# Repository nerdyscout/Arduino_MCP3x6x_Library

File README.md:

# Arduino MCP3x6x Library

Arduino library for Microchip MCP346xR / MCP356xR 16/24-bit SAR analog-to-digital converters over SPI.

Supports Microchip MCP3461R/MCP3462R/MCP3464R (16-bit) and MCP3561R/MCP3562R/MCP3564R (24-bit) ADC families.

## Features

- Template-based device support — one code base for all six MCP3x6xR variants
- SPI register interface with fast commands (CONVERSION, STANDBY, SHUTDOWN, FULL_SHUTDOWN, RESET, SREAD, IREAD, IWRITE)
- Single-ended and differential channel selection (CH0–CH7, internal channels: OFFSET, VCM, AVDD, TEMP, DIFFx)
- Config0–Config3 register access (gain, OSR, data rate, conversion mode, etc.)
- Continuous conversion and scan modes
- Data-ready (DR) status and data-available polling
- IRQ and MCLK pin attachment
- Offset / gain calibration and temperature conversion helpers
- Low-power modes: standby, shutdown, full shutdown
- PlatformIO-mocked unit tests (ArduinoFake + Unity), hardware smoke tests, and hardware-in-the-loop SPI verification

## Supported devices

| Device | Resolution |
|--------|------------|
| MCP3461R / MCP3462R / MCP3464R | 16-bit |
| MCP3561R / MCP3562R / MCP3564R | 24-bit |

## Quick start

### Installation

**Arduino Library Manager:** search for **MCP3x6xR**.

**Manual / git:**

```sh
git clone https://github.com/nerdyscout/Arduino_MCP3x6x_Library.git \
  ~/Arduino/libraries/MCP3x6xR
```

**PlatformIO:** add to `platformio.ini`:

```ini
lib_deps = nerdyscout/MCP3x6xR
```

### Basic usage

```cpp
#include "Arduino_MCP3x6x_Library.hpp"

MCP3461 mcp;  // or MCP3564, MCP3464, etc.

void setup() {
  mcp.begin();
}

void loop() {
  int32_t raw = mcp.analogRead(MCP3x6x_CH0);
  double volt = raw * mcp.getReference() / mcp.getMaxValue();
  delay(100);
}
```

See `src/Arduino_MCP3x6x_Library.hpp` for the full class API, or build the Doxygen reference (`doxygen Doxyfile`).

## Building and testing

This project uses PlatformIO.

### Build examples

Build all examples for all environments:

```sh
./examples/build.sh
```

Build specific environments:

```sh
./examples/build.sh ESP32 ATMEGA328P SAMD21G18A
```

Build only one example:

```sh
./examples/build.sh MCP3564_DMA
```

Upload a single example to your board:

```sh
./examples/upload.sh MCP3564_DMA ATMEGA328P
```

See `examples/README.md` for full `build.sh` / `upload.sh` usage details.

### Run mocked unit tests (no hardware required)

```sh
pio test -e mocked
```

The mocked environment compiles and executes the same mock test suite for all six MCP variants via `FOR_EACH_ADC` macro expansion, verifying chip-ID validation and per-variant register behavior.

### Hardware smoke test (real board)

Build and upload the hardware smoke test to a physical board (default: `ATMEGA328P` / Arduino Nano):

```sh
pio test -e ATMEGA328P
```

Select the MCP variant with `-DTEST_ADC_TYPE=<variant>`:

```sh
pio test -e ATMEGA328P --build-flags "-DTEST_ADC_TYPE=MCP3564"
```

### Hardware-in-the-loop test (real board + Unity Serial readback)

```sh
# Run on default ATMEGA328P / MCP3564
pio run -t test_hil -e ATMEGA328P

# Run with a specific MCP variant
pio run -t test_hil -e ATMEGA328P --build-flags "-DTEST_ADC_TYPE=MCP3464"
```

### SPI communication test (real board + oscilloscope readback)

Verify real SPI transactions end-to-end using the `test_hil_spi` custom target:

```sh
pio run -t test_hil_spi -e ATMEGA328P
pio run -t test_hil_spi -e ATMEGA328P --build-flags "-DTEST_ADC_TYPE=MCP3464"
```

See `test/README.md` for the full testing guide (mocked, hardware, HIL, and SPI HIL).

## PCB fabrication

The `pcb/` directory contains KiCad projects and KiBot configs for three reference boards:

| Board | Top render | Bottom render |
|-------|------------|---------------|
| Adafruit Feather | [Feather_top.svg](pcb/Adafruit/Feather_top.svg) | [Feather_bottom.svg](pcb/Adafruit/Feather_bottom.svg) |
| Arduino Uno | [Uno_top.svg](pcb/Arduino/Uno_top.svg) | [Uno_bottom.svg](pcb/Arduino/Uno_bottom.svg) |
| Sparkfun ProMicro | [ProMicro_top.svg](pcb/Sparkfun/ProMicro_top.svg) | [ProMicro_bottom.svg](pcb/Sparkfun/ProMicro_bottom.svg) |

Generate top/bottom board renders and fabrication zips:

```sh
./pcb/kibot.sh
```

- `pcb/render.kibot.yaml` — board renders
- `pcb/fab.kibot.yaml` — fabrication outputs

Outputs are written next to each `.kicad_pcb` file in `pcb/`. See `pcb/README.md` for details.

## Documentation

- `pcb/README.md` — PCB fabrication (KiBot renders and fabrication zips)
- `examples/README.md` — Examples build and upload
- `test/README.md` — Native, hardware, and HIL testing
- `docs/` — Doxygen API reference (`doxygen Doxyfile`), also hosted at https://nerdyscout.github.io/Arduino_MCP3x6x_Library/

## Contributing

See `pcb/README.md`, `examples/README.md`, and `test/README.md` for domain-specific guides. Submit changes via pull request against `develop`.

## License

MIT. See `LICENSES` for details.

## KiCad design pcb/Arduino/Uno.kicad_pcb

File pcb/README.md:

# PCB Fabrication

Generate top/bottom board renders and fabrication zips:

```sh
./pcb/kibot.sh
```

KiBot config files:
- `pcb/render.kibot.yaml` — board renders
- `pcb/fab.kibot.yaml` — fabrication outputs

Outputs are written next to each `.kicad_pcb` file in `pcb/`.

## Board renders

| Board | Top | Bottom |
|-------|-----|--------|
| Adafruit Feather | [Feather_top.svg](Adafruit/Feather_top.svg) | [Feather_bottom.svg](Adafruit/Feather_bottom.svg) |
| Arduino Uno | [Uno_top.svg](Arduino/Uno_top.svg) | [Uno_bottom.svg](Arduino/Uno_bottom.svg) |
| Sparkfun ProMicro | [ProMicro_top.svg](Sparkfun/ProMicro_top.svg) | [ProMicro_bottom.svg](Sparkfun/ProMicro_bottom.svg) |

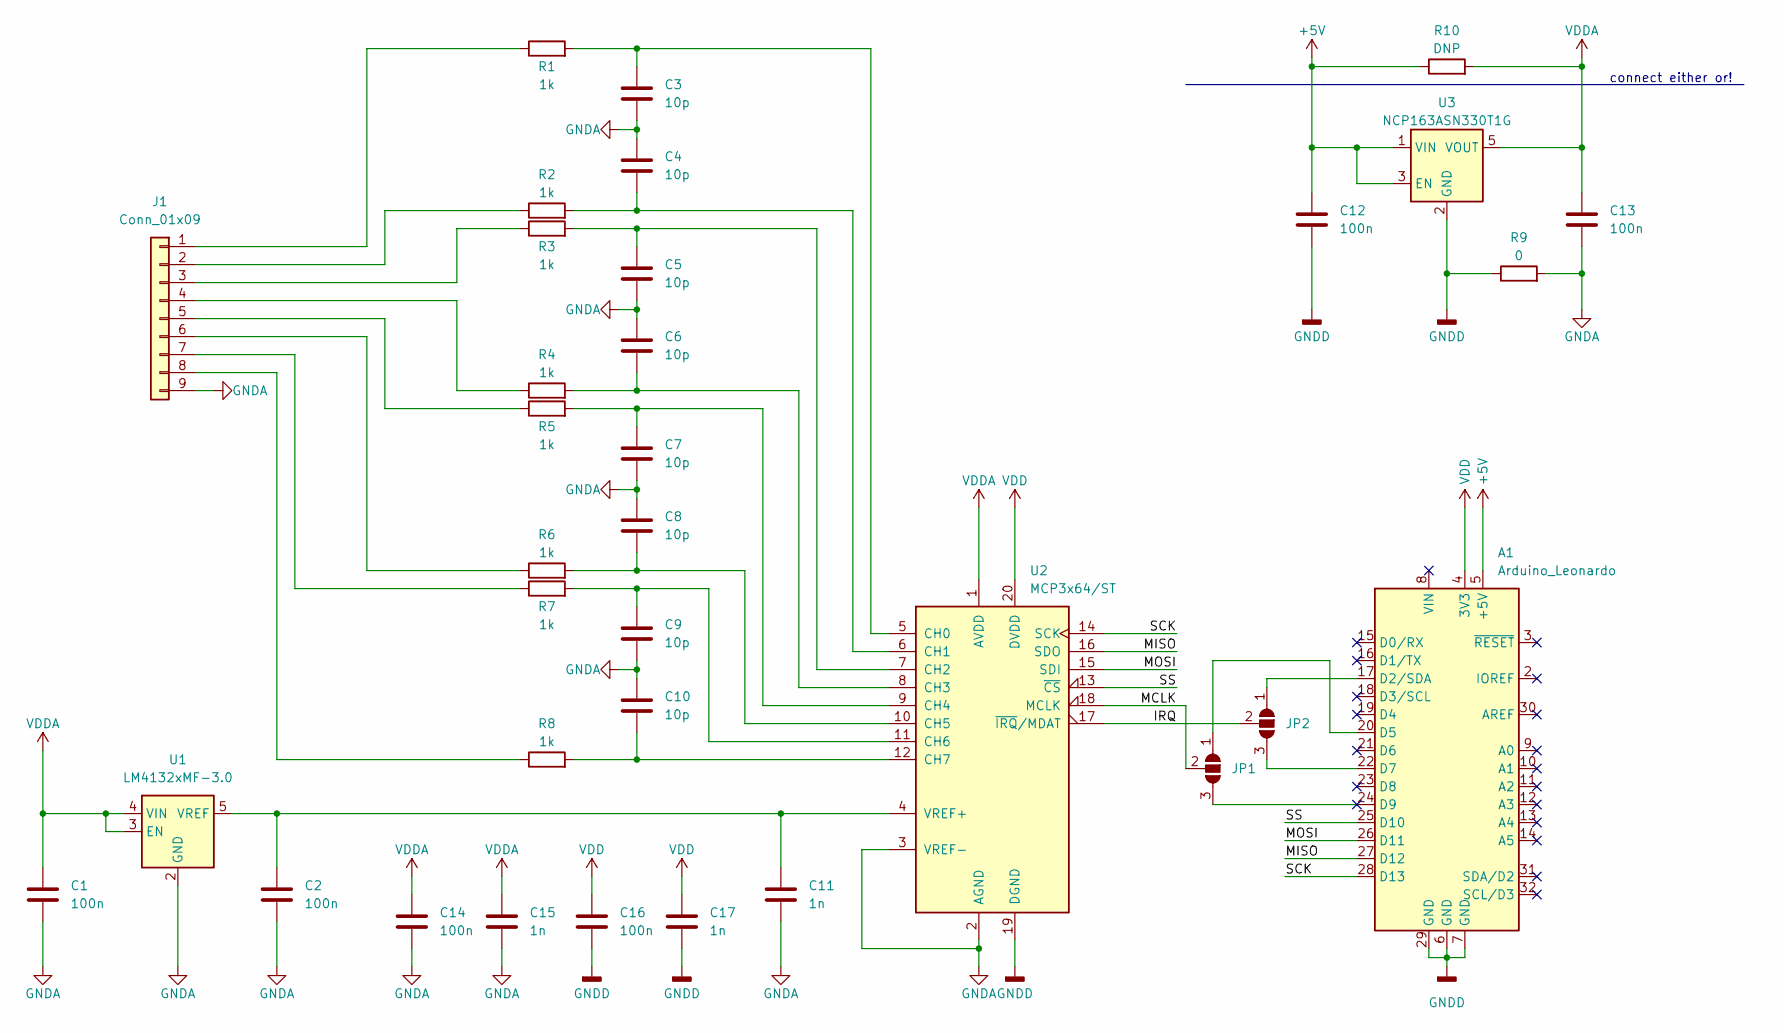
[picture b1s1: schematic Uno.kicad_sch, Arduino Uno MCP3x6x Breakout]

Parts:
A1: Arduino_Leonardo; Arduino_UNO_R3
C1, C2, C12, C13, C14, C16: 100n; C_0603_1608Metric
C3, C4, C5, C6, C7, C8, C9, C10: 10p; C_0402_1005Metric
C11, C15, C17: 1n; C_0603_1608Metric
J1: Conn_01x09; TerminalBlock_Phoenix_MKDS-3-9-5.08_1x09_P5.08mm_Horizontal
JP1, JP2: SolderJumper_3_Open; SolderJumper-3_P1.3mm_Open_RoundedPad1.0x1.5mm
R1, R2, R3, R4, R5, R6, R7, R8: 1k; R_0402_1005Metric
R9: 0; R_0603_1608Metric
R10: DNP; R_0603_1608Metric
U1: LM4132xMF-3.0; SOT-23-5
U2: MCP3x64/ST; TSSOP-20_4.4x6.5mm_P0.65mm
U3: NCP163ASN330T1G; SOT-23-5

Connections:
+5V: A1.5 (+5V), C12.1, R10.1, U3.1 (VIN), U3.3 (EN)
/IRQ: JP2.2 (C), U2.17 (~IRQ/MDAT)
/MCLK: JP1.2 (C), U2.18 (MCLK)
/MISO: A1.27 (D12), U2.16 (SDO)
/MOSI: A1.26 (D11), U2.15 (SDI)
/SCK: A1.28 (D13), U2.14 (SCK)
/SS: A1.25 (D10), U2.13 (~CS)
GNDA: C1.2, C2.2, C3.2, C4.1, C5.2, C6.1, C7.2, C8.1, C9.2, C10.1, C11.2, C13.2, C14.2, C15.2, J1.9, R9.2, U1.2 (GND), U2.2 (AGND), U2.3 (VREF-)
GNDD: A1.6 (GND), A1.7 (GND), A1.29 (GND), C12.2, C16.2, C17.2, R9.1, U2.19 (DGND), U3.2 (GND)
unnamed: A1.17 (D2/SDA), JP2.1 (A)
unnamed: A1.20 (D5), JP1.1 (A)
unnamed: A1.22 (D7), JP2.3 (B)
unnamed: C3.1, R1.2, U2.5 (CH0)
unnamed: C4.2, R2.2, U2.6 (CH1)
unnamed: C5.1, R3.2, U2.7 (CH2)
unnamed: C6.2, R4.2, U2.8 (CH3)
unnamed: C7.1, R5.2, U2.9 (CH4)
unnamed: C8.2, R6.2, U2.10 (CH5)
unnamed: C9.1, R7.2, U2.11 (CH6)
unnamed: C10.2, R8.2, U2.12 (CH7)
unnamed: C2.1, C11.1, U1.5 (VREF), U2.4 (VREF+)
unnamed: J1.1, R1.1
unnamed: J1.2, R2.1
unnamed: J1.3, R3.1
unnamed: J1.4, R4.1
unnamed: J1.5, R5.1
unnamed: J1.6, R6.1
unnamed: J1.7, R7.1
unnamed: J1.8, R8.1
VDD: A1.4 (3V3), C16.1, C17.1, U2.20 (DVDD)
VDDA: C1.1, C13.1, C14.1, C15.1, R10.2, U1.3 (EN), U1.4 (VIN), U2.1 (AVDD), U3.5 (VOUT)

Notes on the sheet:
connect either or!

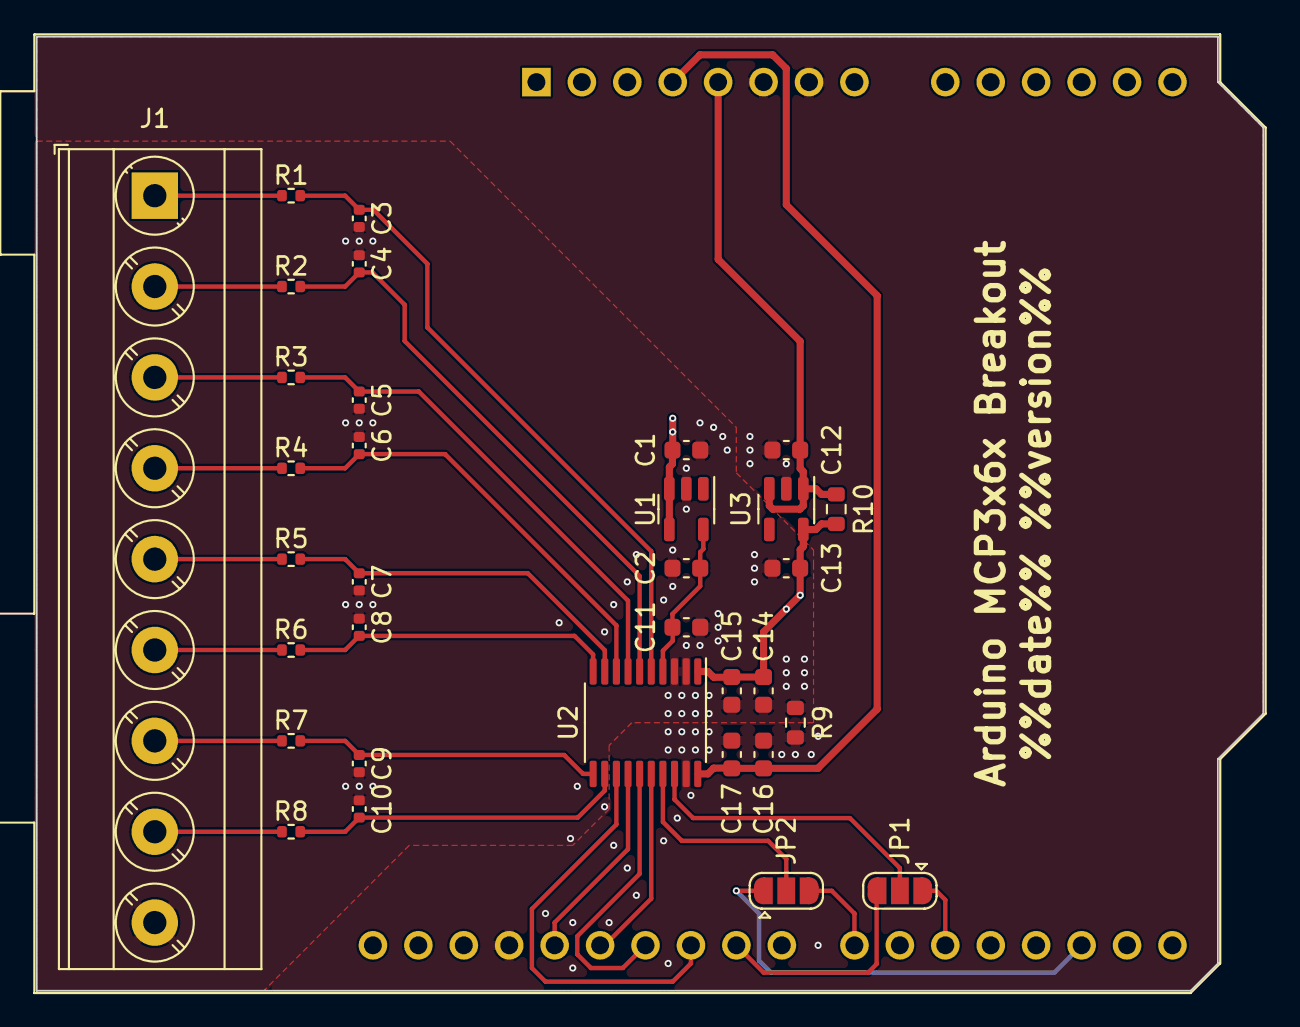
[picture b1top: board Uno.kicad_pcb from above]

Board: 2 copper layers, 68.6 x 53.3 mm, 34 parts (0 on the bottom side), 31 nets.

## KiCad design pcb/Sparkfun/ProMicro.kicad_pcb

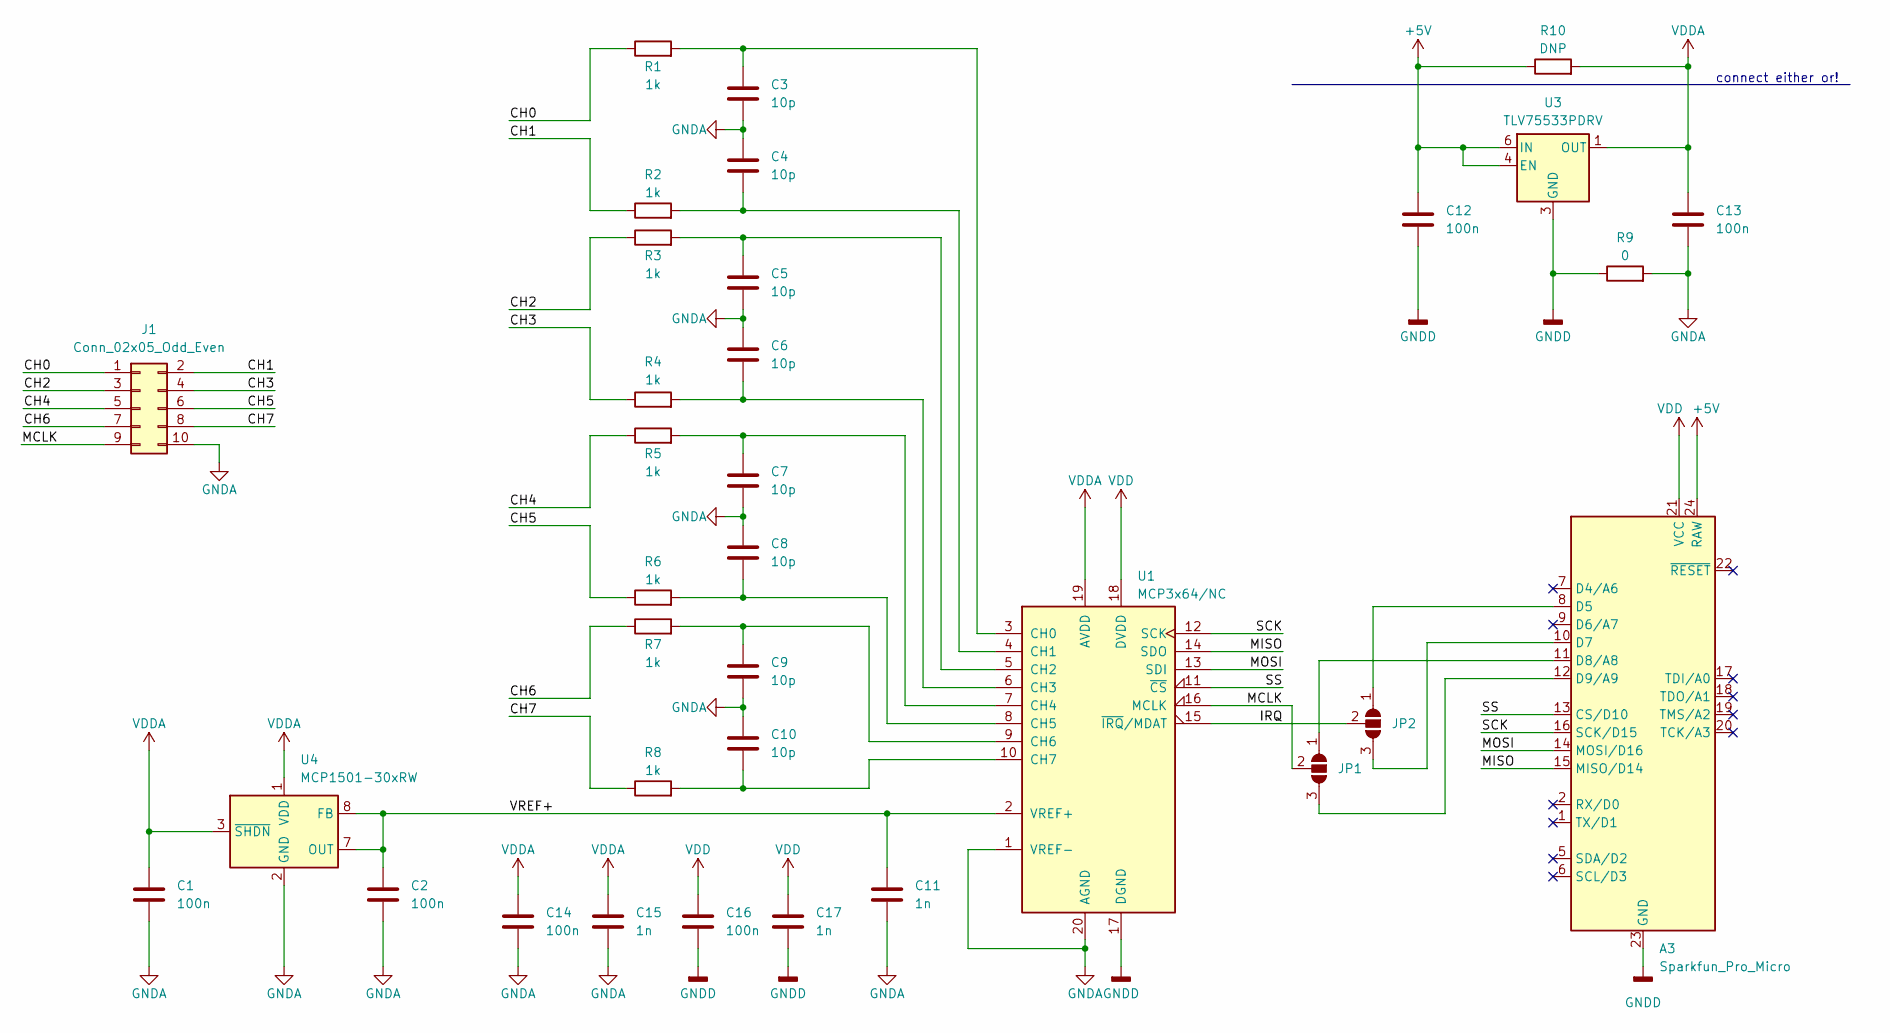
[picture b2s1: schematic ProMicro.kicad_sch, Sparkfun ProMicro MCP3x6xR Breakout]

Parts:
A3: Sparkfun_Pro_Micro; ProMicro
C1, C2, C12, C13, C14, C16: 100n; C_0402_1005Metric
C3, C4, C5, C6, C7, C8, C9, C10: 10p; C_0402_1005Metric
C11, C15, C17: 1n; C_0402_1005Metric
J1: Conn_02x05_Odd_Even; PinSocket_2x05_P2.54mm_Horizontal
JP1, JP2: SolderJumper_3_Open; SolderJumper-3_P1.3mm_Open_RoundedPad1.0x1.5mm
R1, R2, R3, R4, R5, R6, R7, R8: 1k; R_0402_1005Metric
R9: 0; R_0402_1005Metric
R10: DNP; R_0402_1005Metric
U1: MCP3x64/NC; QFN-20-1EP_3x3mm_P0.4mm_EP1.65x1.65mm_ThermalVias
U3: TLV75533PDRV; WSON-6-1EP_2x2mm_P0.65mm_EP1x1.6mm
U4: MCP1501-30xRW; WDFN-8-1EP_2x2mm_P0.5mm_EP0.8x1.2mm

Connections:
+5V: A3.24 (RAW), C12.1, R10.1, U3.4 (EN), U3.6 (IN)
/CH0: J1.1, R1.1
/CH1: J1.2, R2.1
/CH2: J1.3, R3.1
/CH3: J1.4, R4.1
/CH4: J1.5, R5.1
/CH5: J1.6, R6.1
/CH6: J1.7, R7.1
/CH7: J1.8, R8.1
/IRQ: JP2.2 (C), U1.15 (~IRQ/MDAT)
/MCLK: J1.9, JP1.2 (C), U1.16 (MCLK)
/MISO: A3.15 (MISO/D14), U1.14 (SDO)
/MOSI: A3.14 (MOSI/D16), U1.13 (SDI)
/SCK: A3.16 (SCK/D15), U1.12 (SCK)
/SS: A3.13 (CS/D10), U1.11 (~CS)
/VREF+: C2.1, C11.1, U1.2 (VREF+), U4.7 (OUT), U4.8 (FB)
GNDA: C1.2, C2.2, C3.2, C4.1, C5.2, C6.1, C7.2, C8.1, C9.2, C10.1, C11.2, C13.2, C14.2, C15.2, J1.10, R9.2, U1.1 (VREF-), U1.20 (AGND), U4.2 (GND), U4.4 (GND), U4.5 (GND), U4.6 (GND), U4.9
GNDD: A3.3 (GND), A3.4 (GND), A3.23 (GND), C12.2, C16.2, C17.2, R9.1, U1.17 (DGND), U1.21, U3.3 (GND), U3.7 (GND)
unnamed: A3.8 (D5), JP2.1 (A)
unnamed: A3.10 (D7), JP2.3 (B)
unnamed: A3.11 (D8/A8), JP1.1 (A)
unnamed: A3.12 (D9/A9), JP1.3 (B)
unnamed: C3.1, R1.2, U1.3 (CH0)
unnamed: C4.2, R2.2, U1.4 (CH1)
unnamed: C5.1, R3.2, U1.5 (CH2)
unnamed: C6.2, R4.2, U1.6 (CH3)
unnamed: C7.1, R5.2, U1.7 (CH4)
unnamed: C8.2, R6.2, U1.8 (CH5)
unnamed: C9.1, R7.2, U1.9 (CH6)
unnamed: C10.2, R8.2, U1.10 (CH7)
VDD: A3.21 (VCC), C16.1, C17.1, U1.18 (DVDD)
VDDA: C1.1, C13.1, C14.1, C15.1, R10.2, U1.19 (AVDD), U3.1 (OUT), U4.1 (VDD), U4.3 (~SHDN)

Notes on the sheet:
connect either or!

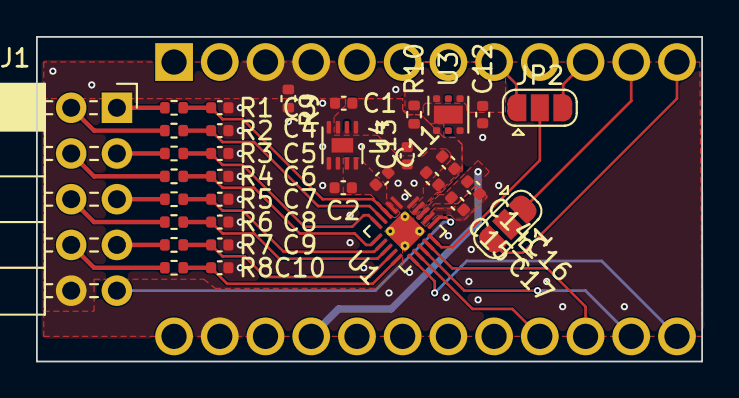
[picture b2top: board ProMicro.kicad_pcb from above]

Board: 2 copper layers, 37.0 x 18.0 mm, 34 parts (1 on the bottom side), 32 nets.

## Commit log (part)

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2022-01-02 init first draft of project
2022-01-23 update almost everything
2022-05-29 resolved a few issuses
2022-06-30 still no good
2022-07-01 Fixed License File Name
2022-07-01 Changed Badge Color
2022-08-08 refactored
2022-08-26 just another refactor
2022-09-02 cleaning up things
2022-09-04 fixes
2022-09-04 updating docs
2022-09-04 set/get voltage reference or use internal default
2022-09-04 setting custom solution, does not have any effect yet
2022-09-05 starting adding structure from teendy adc lib
2022-09-09 move defaults inside of class
2022-09-11 rework resolution and reference
2022-09-16 adding a lot things to behave like teensy ADC lib
2022-09-16 update samples
2022-10-29 reverse receive array only
2022-10-29 just moved lines togehter
2022-10-29 add functin to set over sampling rate
2022-10-29 cleanup code
2022-10-29 update docu
2022-10-30 adding doxygen docu generation
2022-10-30 more docu
2022-10-30 adding datasheets
2022-10-31 update sample code without actual testing it
2022-11-04 importend fixes
2022-11-20 Added ability to set gain
2022-12-03 Fixed union structure size assignments, analogRead
2022-12-03 disable all interrupts while SPI transfer
2022-12-03 output serial info only in debug build
2022-12-03 update actions
2022-12-03 remove optional parameter
2022-12-03 use web pdf instead of inside repo
2022-12-09 Print to serial only in debug mode
2022-12-10 modify when workflows run
2022-12-10 deploy: 4d00da90100cf651cd27d3e3fcba1da4cd59bc75
2022-12-29 adding unit tests
2022-12-30 adding two sample pcbs
2022-12-30 lint formating
2022-12-30 make SPI speed and adress overrideable from outside of lib
2022-12-30 adding kibot
2022-12-30 fix drc
2023-01-16 Added Boost Functionality
2023-01-16 [pre-commit.ci] auto fixes from pre-commit.com hooks
    for more information, see https://pre-commit.ci
2023-05-15 fix (test): native tests are running
2023-05-17 test
2023-10-09 Update .pre-commit-config.yaml
    add clang-format for pre-commit-hook
2023-10-09 Update .pre-commit-config.yaml
    fix spaces
2023-10-09 Update .pre-commit-config.yaml
    use explicit version
2023-10-10 [pre-commit.ci] pre-commit autoupdate (#6)
    * [pre-commit.ci] pre-commit autoupdate
    updates:
    - [github.com/pre-commit/pre-commit-hooks: v4.3.0 → v4.5.0](https://github.com/pre-commit/pre-commit-hooks/compare/v4.3.0...v4.5.0)
    * Update .pre-commit-config.yaml
    add clang-format for pre-commit-hook
    * Update .pre-commit-config.yaml
2023-10-10 add R
2023-10-10 move code
2023-10-10 fix cpplint things
2023-10-10 use enum instead of strongly txped enum classes
2023-10-15 add examples
2023-10-15 test runs on hardware
2023-10-15 make PSPI address and speed changeable from outside of header file
2023-11-02 add (test): setup regression tests on real hardware
2023-11-28 default settings
2023-12-27 Reintroduce interrupt management
2024-01-23 fix union struct according #5
2024-01-24 Pull develop branch into 370
2024-02-04 adding Arduino.h to all examples
2024-02-17 make useage of Settings class in begin function
2024-02-20 major changes to begin function
2024-02-21 reworked settings
2024-02-21 update pcbs
2024-02-28 move samd and add esp32s2
2024-02-28 ongoing refactore
2024-03-25 Zero-initialize buffer used for ADC reads (#14)
2024-04-19 it builds
2024-08-07 remove main
2024-10-07 [pre-commit.ci] pre-commit autoupdate
    updates:
    - [github.com/pre-commit/pre-commit-hooks: v4.5.0 → v5.0.0](https://github.com/pre-commit/pre-commit-hooks/compare/v4.5.0...v5.0.0)
2025-01-31 docs: add brief description
2025-01-31 test: reorganize tests
2025-02-01 remove Settings() tests
2025-02-01 wait for native Serial on tests
2025-02-02 separate namespace
2025-02-04 namespace
2025-10-13 chore: update reuse
2025-10-13 chore: update version
2026-06-20 fix: swap MISO/MOSI in constructor pin order to match README documentation
2026-06-20 fix: compare against desired register values in configure() instead of hardcoded defaults
2026-06-20 fix: enable enableScanChannel() and disableScanChannel() by uncommenting loop bodies
2026-06-20 fix: update _result union in analogRead() scan branch before returning
2026-06-20 test: add native unit tests with ArduinoFake for all bug fixes
    - Add native_ci env to platformio_ci.ini for host-based testing
    - Add flush() override to MCP3x6x for ArduinoFake Stream compatibility
    - Conditionally include ArduinoFake.h in library header under PIO_NATIVE_TESTING
    - Rewrite test file with 19 comprehensive tests covering all 6 critical bug fixes
    - Tests validate configure() register writes, scan channel enable/disable,
    analogReadDifferential busy-wait, and constructor behavior
2026-06-20 BUG-2: Fix STATUS byte bitfield mapping per datasheet
    POR=bit5, CRCCFG=bit4, DR=bit3 per MCP3461/3561 datasheet.
    Old code mapped them to bits 0/1/2, breaking POR detection,
    busy-wait loops (DR), and isComplete().
    Also updated test mock default return from 0x05 to 0x14
    to match corrected POR (bit4) and DR (bit2) positions.
2026-06-20 BUG-4: Fix _getValue() sign extension using arithmetic shift
    Old code used bitWrite/bitClear to copy sign bit to bit 31 then
    cleared the original sign bit, which destroyed negative values
    (e.g. 0x800000 became 0x80000000 instead of 0xFF800000).
    Fix: use arithmetic right shift for SGN_DATA:
    16-bit: (int32_t)(raw << 16) >> 16
    24-bit: (int32_t)(raw << 8) >> 8
2026-06-20 BUG-3: Fix multi-byte register writes byte order
    SCAN, TIMER, OFFSET, GAIN, CRCCFG writes sent raw[0] first (LSB)
    but device expects MSB-first. Added _reverse_array() before
    _transfer() for all multi-byte write functions, matching the
    approach already used for ADCDATA reads.
    Updated SCAN test to check byte [2] (last byte after reversal)
    instead of byte [0] for channel bit detection.
2026-06-20 BUG-6: Fix analogRead() scan mode restarting scan cycle
    Removed conversion() call from scan branch — it restarted the
    scan cycle and lost other channels' data. Now returns cached
    _result value for the requested channel.
2026-06-20 BUG-7 + INACC-1: Fix unlock() and LOCK default
    BUG-7: unlock() wrote cached _lock (0x00 after INACC-1, or 0xA5
    previously) which re-locked the device. Now writes 0x00 to unlock.
    INACC-1: MCP3x6x_CFG_LOCK default was 0xA5 (lock password) but
    device defaults to 0x00 (unlocked) after POR. Changed to 0x00
    so cached value matches hardware state after begin()/reset().
2026-06-20 Fix documentation issues and improvements
    DOC-1: Update README constructor signatures to match actual code:
    SPIClass* after pinCLK (not before pinMOSI), scan-mode
    constructor requires all 6 pins (no ambiguity).
    DOC-5: Update MCLK note — it IS implemented via attachMCLK()/tone().
    DOC-6: Remove unused MCP34x1/356x_DEVICE_TYPE defines.
    IMP-1: Add startScan() method that configures IRQ pin (irq_mode=01,
2026-06-20 Update README, keywords.txt, library.properties, AGENTS.md
    README: Fix constructor signatures (SPIClass* at end), fix typos,
    update scan-mode usage, remove 'not implemented' MCLK note.
    keywords.txt: Populate with all 7 class types, ~50 methods, ~80
    constants per Arduino IDE keyword format.
    library.properties: Fix 'MPC3x6xR' -> 'MCP3x6xR' typo.
    AGENTS.md: Mark all BUG/INACC/IMP/DOC items as FIXED with commit
2026-06-20 test(test_analog): remove redundant setUp() calls in tests with single assertion
    - test_analogRead_scan_mode_no_spi: removed 5 setUp() calls between
    sequential setup operations
    - test_analogReadContinuous_continuous_mode: removed 1 setUp() call
    between begin() and startContinuous()
    AI-authored-by: opencode
2026-06-20 chore: enable skipping check of packages
2026-06-20 fix: remove 6-pin constructor, add startScan() to scan examples
    - Remove the 6-pin scan constructor — single 4-pin constructor is the only one
    - Add startScan() calls to all 3 scan-mode examples and src/main.cpp
    - Remove test_scan_constructor and createADCScan() helper
    - Update constructor doc comment
2026-06-20 fix: auto-set ID_SGNEXT_DATA format in startScan()
    startScan() now configures the data format to ID_SGNEXT_DATA so that
    _getChannel() can extract the channel ID from the ADC data bits [31:28]
    instead of incorrectly using _mux.raw, which is wrong in scan mode.
2026-06-20 fix: add static_assert to Stream::read() for AVR truncation
    Stream::read() returns int which is 16-bit on AVR platforms. 24-bit
    ADC values would be silently truncated. Added static_assert that
    triggers a compile error when sizeof(int) < 4 and _MAX_RESOLUTION > 16,
    pointing users to analogRead() instead.
2026-06-20 fix: guard destructor against zero-valued pinIRQ/pinMCLK
    In mux mode _pinIRQ and _pinMCLK are 0. Calling detachInterrupt(0) or
    noTone(0) may be valid pin numbers on some platforms, causing unintended
    side effects. Now guarded with if() checks.
2026-06-20 fix: remove unused _channel_mask member
2026-06-20 fix: analogReadContinuous() uses loop index i, not _adcdata.channelid
    The channel lookup loop finds the matching channel at index i, so the
    returned value should come from _result.raw[i], not from the stale
    _adcdata.channelid which may reference a different channel.
2026-06-20 fix: peek() returns -1 (no data) instead of 1
    Stream::peek() by convention returns -1 when no data is available.
    Previously returned 1 unconditionally which was misleading.
2026-06-20 fix: add _dataAvailable flag for reliable available() in scan mode
    IRQ_handler() sets _dataAvailable=true, analogRead() and Stream::read()
    clear it. available() returns this flag instead of polling status_dr(),
    which is unreliable in scan mode (DR comes from IRQ pin, not SPI status).
2026-06-20 refactor: rename examples to {ADC}_{Mode}_{Feature}, add 5 config examples
    Rename all 6 existing examples:
    {Mode}_{SubMode}_{ADC} → {ADC}_{Mode}_{Feature}
    e.g. SingleEnded_Mux_MCP3461 → MCP3461_Mux_SingleEnded
    Add 5 new configuration-focused examples:
    MCP3461_Mux_InternalChannels — read TEMP sensor + AVDD voltage
    MCP3462_Scan_Stream — Stream::available() / read() polling
2026-06-20 docs: update README.md for single-constructor, 11 examples
    README.md:
    - Single constructor, two modes explained with code snippets
    - Scan mode setup sequence: attachIRQ + attachMCLK + enableScanChannel + startScan
    - Full example table with all 11 examples
2026-06-20 test: renamed common test file
2026-06-20 feat: add toVoltage, readTemperature, timeout, and chip ID detection
    - toVoltage(int32_t raw): raw ADC to microvolts using VREF and gain
    - readTemperature(): TEMP channel to centi-Celsius with calibration setters
    - setReadTimeout(ms): global timeout for analogRead/analogReadDifferential
    - Chip ID/R-variant validation in begin() with auto VREF configuration
2026-06-20 feat: low-priority features — type aliases, peek, irq_mode enum, scan bit fix
    - Add MCP3465/MCP3565 type aliases (2-channel UQFN variants)
    - peek() returns cached ADC value when data available
    - Add getDeviceAddress() for multi-device bus verification
    - irq_mode typed enum (IRQ_OFF/IRQ_OPEN_DRAIN/IRQ_PUSH_PULL_LOW/IRQ_PUSH_PULL_HIGH)
    - irq() and startScan() use enum parameters
    - SCAN reserved bit 20 forced to 0 in write(Scan)
2026-06-22 [pre-commit.ci] pre-commit autoupdate
    updates:
    - [github.com/pre-commit/pre-commit-hooks: v4.5.0 → v6.0.0](https://github.com/pre-commit/pre-commit-hooks/compare/v4.5.0...v6.0.0)
2026-06-29 refactor: purge Stream class, replace with dataAvailable()/readADCDATA()
    - Remove : public Stream inheritance
    - Remove flush(), available(), read(), write(), peek() overrides
    - Add dataAvailable() and readADCDATA() as non-virtual replacements
    - Update MCP3462_Scan_Stream example to use new API
    - Remove 4 obsolete Stream tests, rename test_available -> test_dataAvailable

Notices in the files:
pcb/Arduino/Uno.kicad_pcb:
CERN-OHL-S-2.0
